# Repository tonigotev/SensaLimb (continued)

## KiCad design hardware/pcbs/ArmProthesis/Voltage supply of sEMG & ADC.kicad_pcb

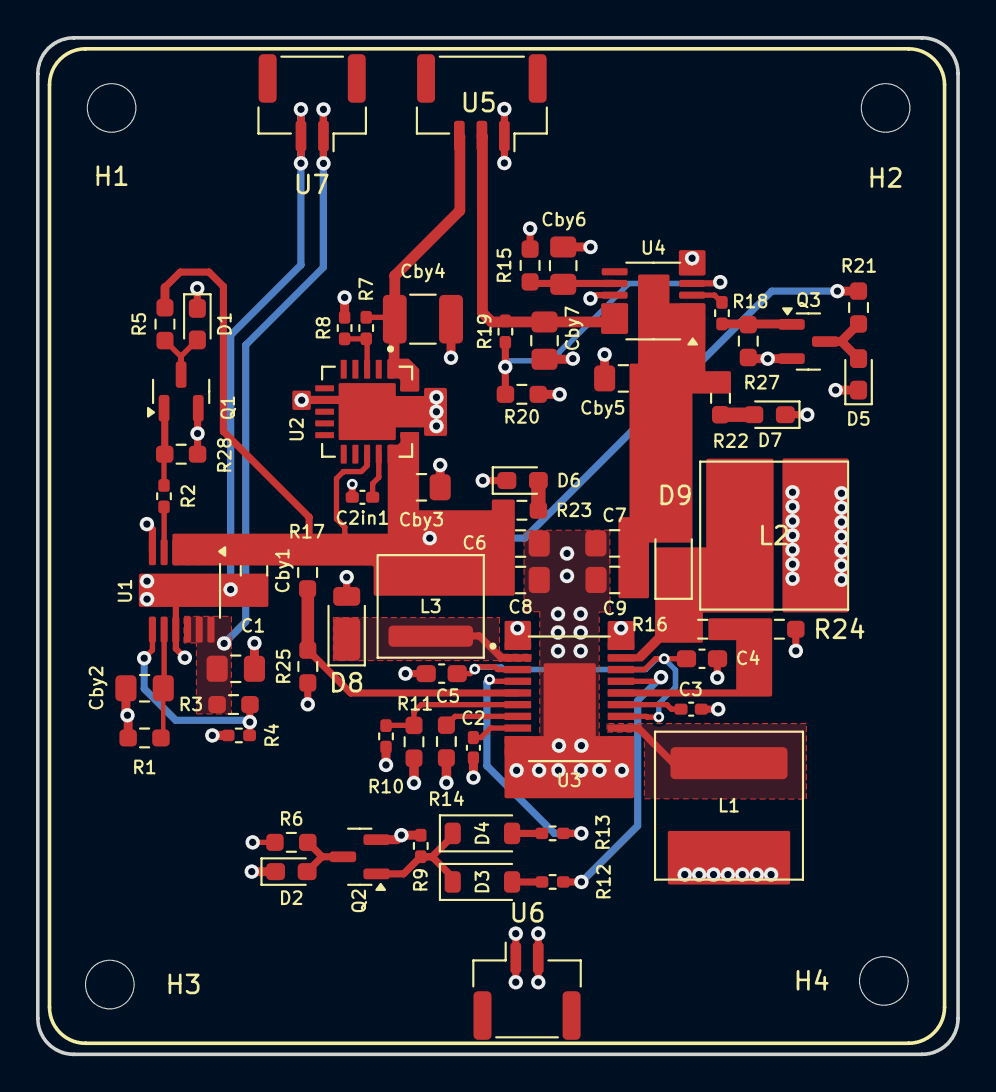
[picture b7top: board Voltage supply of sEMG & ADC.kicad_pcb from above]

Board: 4 copper layers, 51.1 x 56.5 mm, 70 parts (0 on the bottom side), 37 nets.

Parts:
C1, C6, C7, C8, C9: 10uF; C_0805_2012Metric_Pad1.18x1.45mm_HandSolder
C2, C3: 100nF; C_0402_1005Metric_Pad0.74x0.62mm_HandSolder
C2in1: 1uF; C_0402_1005Metric_Pad0.74x0.62mm_HandSolder
C4, C5: 1uF; C_0603_1608Metric_Pad1.08x0.95mm_HandSolder
Cby1, Cby3, Cby5, Cby7: 10uF; C_0805_2012Metric_Pad1.18x1.45mm_HandSolder
Cby2: 0.47uF; C_0805_2012Metric_Pad1.18x1.45mm_HandSolder
Cby4: 47uF; C_1210_3225Metric_Pad1.33x2.70mm_HandSolder
Cby6: 4.7uF; C_0805_2012Metric_Pad1.18x1.45mm_HandSolder
D1, D2, D5, D6, D7: LED; LED_0603_1608Metric_Pad1.05x0.95mm_HandSolder
D3, D4: D; D_SOD-123
D8: DFLS240L; D_PowerDI-123
D9: DFLS240; D_PowerDI-123
H1, H2, H3, H4: MountingHole; MountingHole_2.7mm_M2.5_DIN965
L1, L2: 6.8uH; L_Coilcraft_XAL7030-102
L3: 3.3uH; L_Coilcraft_XAL5030-XXX
Q1, Q2, Q3: BC817; SOT-23
R1: 49.9k; R_0603_1608Metric_Pad0.98x0.95mm_HandSolder
R2, R4, R8, R9, R12, R13, R18, R19: 10k; R_0402_1005Metric_Pad0.72x0.64mm_HandSolder
R3: 145k; R_0603_1608Metric_Pad0.98x0.95mm_HandSolder
R5, R6, R21: 5k; R_0603_1608Metric_Pad0.98x0.95mm_HandSolder
R7: 29.4k; R_0402_1005Metric_Pad0.72x0.64mm_HandSolder
R10: 23.7k; R_0402_1005Metric_Pad0.72x0.64mm_HandSolder
R11: 3.48k; R_0603_1608Metric_Pad0.98x0.95mm_HandSolder
R14: 85k; R_0603_1608Metric_Pad0.98x0.95mm_HandSolder
R15: 54.9k; R_0603_1608Metric_Pad0.98x0.95mm_HandSolder
R16, R17: 68k; R_0603_1608Metric_Pad0.98x0.95mm_HandSolder
R20: 147k; R_0603_1608Metric_Pad0.98x0.95mm_HandSolder
R22, R23: 1k; R_0603_1608Metric_Pad0.98x0.95mm_HandSolder
R24, R25, R27, R28: 10k; R_0603_1608Metric_Pad0.98x0.95mm_HandSolder
U1: LT3045xMSE; MSOP-12-1EP_3x4.039mm_P0.65mm_EP1.651x2.845mm
U2: TPS7A4701RGWR; QFN65P500X500X100-21N
U3: LT8471EFE_TRPBF; SOP65P640X120-21N
U4: LT3094xMSE; MSOP-12-1EP_3x4.039mm_P0.65mm_EP1.651x2.845mm
U5: JST_GH_SM03B-GHS-TB_1x03-1MP_P1.25mm_Horizontal
U6, U7: JST_GH_SM02B-GHS-TB_1x02-1MP_P1.25mm_Horizontal

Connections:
+6V: C6.1, C8.1, Cby1.1, Cby3.1, L3.2, R5.2, R17.1, R21.2, R23.1, U1.1 (IN), U1.2 (IN), U1.3 (IN), U1.4 (EN/UV), U2.13 (EN), U2.15 (IN_15), U2.16 (IN_16)
-6V: C7.2, C9.2, Cby5.1, D9.2 (A), R22.1, U4.1 (IN), U4.2 (IN), U4.3 (EN/UV), U4.13 (IN)
/+5.5V: Cby4.1, R7.1, U2.1 (OUT_1), U2.20 (OUT_20), U5.3
/+5V: C1.1, R3.2, U1.10 (OUTS), U1.11 (OUT), U1.12 (OUT), U7.1
/+11.1V: L1.1, R6.2, R10.2, U3.1 (C1), U3.20 (C2), U6.1
/-5.5V: Cby7.1, R19.1, U4.10 (OUTS), U4.11 (OUT), U4.12 (OUT), U5.2
GND: C1.2, C2.2, C2in1.2, C3.2, C4.1, C5.2, C6.2, C7.1, C8.2, C9.1, Cby1.2, Cby2.2, Cby3.2, Cby4.2, Cby5.2, Cby6.2, Cby7.2, D1.1 (K), D2.1 (K), D5.1 (K), D6.1 (K), D7.1 (K), D8.2 (A), L2.1, Q1.2 (E), Q2.2 (E), Q3.2 (E), R1.2, R4.1, R8.2, R9.2, R11.1, R14.2, R15.2, R20.2, R24.2, R25.2, R27.2, R28.2, U1.6 (ILIM), U1.9 (GND), U1.13 (GND), U2.7 (GND_7), U2.17 (NC_17), U2.18 (NC_18), U2.19 (NC_19), U2.21 (GND_21), U3.9 (SYNC), U3.10 (GND), U3.11 (GND), U3.12 (GND), U3.21 (GND), U4.6 (ILIM), U4.9 (GND), U5.1, U6.2, U7.2
unnamed: D1.2 (A), Q1.3 (C), R5.1
unnamed: D2.2 (A), Q2.3 (C), R6.1
unnamed: D3.2 (A), R12.2
unnamed: D3.1 (K), D4.1 (K), Q2.1 (B), R9.1
unnamed: D4.2 (A), R13.2
unnamed: D5.2 (A), Q3.3 (C), R21.1
unnamed: D6.2 (A), R23.2
unnamed: D7.2 (A), R22.2
unnamed: D8.1 (K), L3.1, U3.2 (E1)
unnamed: D9.1 (K), L2.2, R16.1, U3.19 (E2)
unnamed: Q1.1 (B), R2.2, R28.1
unnamed: Q3.1 (B), R18.2, R27.1
unnamed: R2.1, U1.5 (PG)
unnamed: R3.1, R4.2, U1.7 (PGFB)
unnamed: Cby2.1, R1.1, U1.8 (SET)
unnamed: C2in1.1, U2.14 (NR)
unnamed: R7.2, R8.1, U2.3 (SENSE/FB)
unnamed: L1.2, U3.13 (C3)
unnamed: R17.2, R25.1, U3.5 (FB1)
unnamed: R16.2, R24.1, U3.16 (FB2)
unnamed: R10.1, R11.2, U3.6 (OV/UV)
unnamed: R13.1, U3.4 (PG1)
unnamed: R12.1, U3.17 (PG2)
unnamed: R14.1, U3.7 (RT)
unnamed: C4.2, C5.1, U3.3 (VIN1), U3.14 (SHOUT), U3.18 (VIN2)
unnamed: C2.1, U3.8 (SS1)
unnamed: C3.1, U3.15 (SS2)
unnamed: R18.1, U4.4 (PG)
unnamed: R19.2, R20.1, U4.5 (PGFB)
unnamed: Cby6.1, R15.1, U4.8 (SET)

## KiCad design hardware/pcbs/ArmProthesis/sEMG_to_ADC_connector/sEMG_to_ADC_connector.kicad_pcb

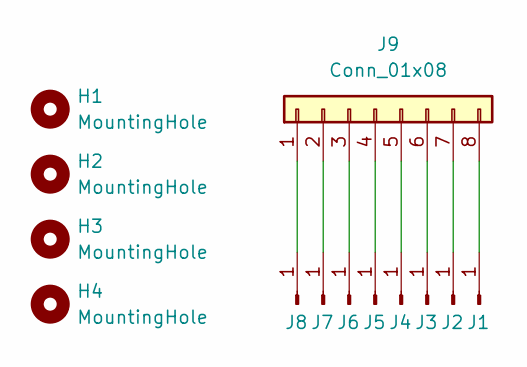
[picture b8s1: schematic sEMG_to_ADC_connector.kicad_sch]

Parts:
H1, H2, H3, H4: MountingHole; MountingHole_2.7mm_M2.5
J1, J2, J3, J4, J5, J6, J7, J8: Conn_01x01_Pin; DIN_Male_1PIN_1.5mm
J9: Conn_01x08; JST_GH_SM08B-GHS-TB_1x08-1MP_P1.25mm_Horizontal

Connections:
unnamed: J1.1, J9.8
unnamed: J2.1, J9.7
unnamed: J3.1, J9.6
unnamed: J4.1, J9.5
unnamed: J5.1, J9.4
unnamed: J6.1, J9.3
unnamed: J7.1, J9.2
unnamed: J8.1, J9.1

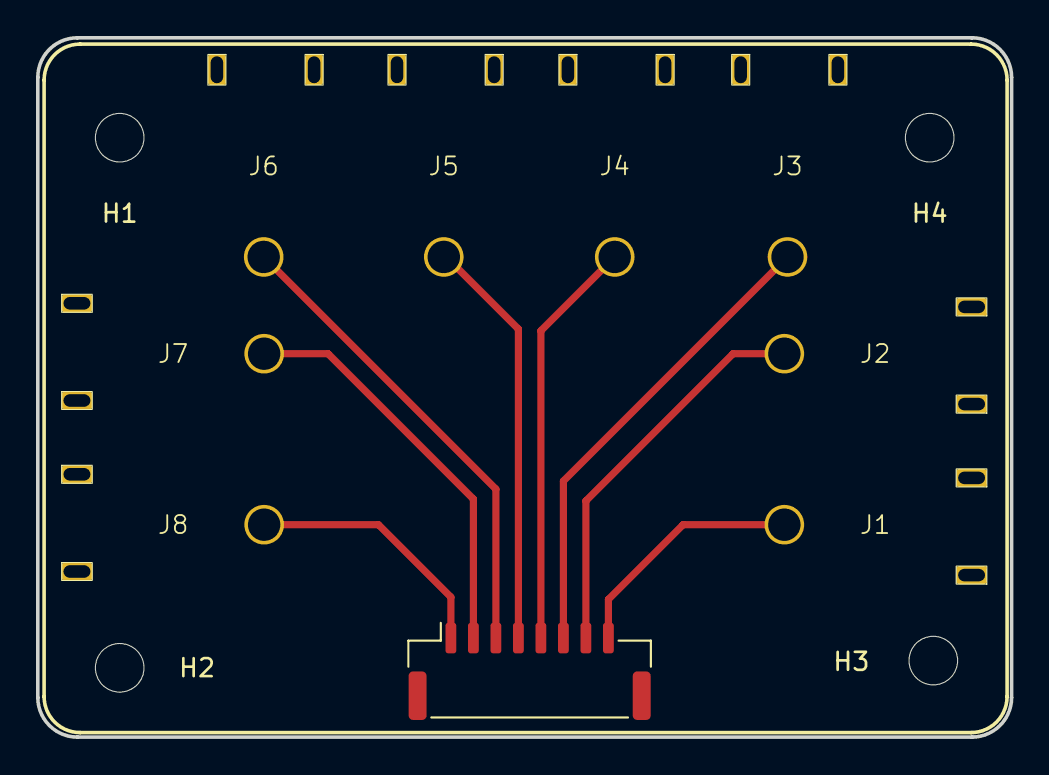
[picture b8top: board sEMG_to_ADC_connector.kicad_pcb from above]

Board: 2 copper layers, 54.1 x 38.9 mm, 13 parts (0 on the bottom side), 8 nets.

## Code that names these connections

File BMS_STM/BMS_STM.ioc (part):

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Mcu.Name=STM32C011F(4-6)Px
Mcu.Package=TSSOP20
Mcu.UserName=STM32C011F6Px
PA13.Mode=Serial_Wire
PA13.Signal=DEBUG_SWDIO
PA14-BOOT0.Mode=Serial_Wire
PA14-BOOT0.Signal=DEBUG_SWCLK
PA2.Mode=Half_duplex(single_wire_mode)
PA2.Signal=USART2_TX
PA8.Signal=GPXTI8
PB6.Mode=I2C
PB6.Signal=I2C1_SCL
PB7.Mode=I2C
PB7.Signal=I2C1_SDA
PC14-OSCX_IN\ (PC14).Mode=LSE-External-Oscillator
PC14-OSCX_IN\ (PC14).Signal=RCC_OSCX_IN
PC15-OSCX_OUT\ (PC15).Mode=LSE-External-Oscillator
PC15-OSCX_OUT\ (PC15).Signal=RCC_OSCX_OUT
RCC.HSE_VALUE=8000000
RCC.SYSCLKFreq_VALUE=12000000
board=custom

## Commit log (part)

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2025-09-12 Voltage supply of sEMG & ADC
2025-09-14 EMG sensor v0.2
2025-09-18 sEMG sensors v0.3
2025-09-18 Fixes
    sEMG - minor
    Voltage supply... - major but not fixed
2025-09-18 Additional to last push
2025-09-18 Voltage supply sEMG & ADC v0.2
    Major fixes. Mounting holes missing
2025-09-21 BMS v0.2v + polishment of Vsupply board
2025-09-21 Connector update of the sEMG sensor
    Changed it to be JST_GH_SM04B instead of JST_GH_BM04B for easier use
2025-09-22 ADC + sEMG changes
    sEMG - connector updates
    ADC - major changes - connectors, layout changes
2025-09-23 BMS v0.3 + main folder reconstruction
2025-09-23 sEMG critical issue
    Corrected inaccurate DIN 1.5mm jack footprint
2025-09-23 Cosmetics xd
2025-10-27 Vs of sEMG and ADC v0.4
2025-11-03 Corrected BMS connection
2025-11-04 BMS v0.5 still not resized
2026-01-13 Mendeley data set + plotter
    Analyzing data sets and beginning to develop the ML algorithm for the arm
2026-01-13 Normalizer + plotter(upgraded
    Normalizer for the data.
    Plotter has new functionalities such as - plot all subjects data and distribute them to new folders, calculate db/frequency for a new plot etc.
2026-01-19 Fix Vsupply
    added important Schottky diodes on the BUCK
2026-01-19 New
    Mendeley dataset is not good enough for angle regression or for 3 class classifier.
    Moved on to Toro Ossaba's dataset specifically designed for training ML algorithms - smooth kinetic transitions.
    Trainers for several ML models have been implemented but the most successful one is conv1d_angle_toro_ossaba. This exact model doesn't extract features but lets the model extrarct them by 3 convoluti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
2026-01-20 Fixed EMG sensors active band pass filter
2026-01-20 new LDO with a proper rail splitter
2026-01-21 Fixed LCSC numbers of the new filter parts
2026-01-24 Fixed compatibility of connectors + new BMS chip
2026-01-24 bms V0.7 with BQ76905
2026-01-28 BMS board fixes
2026-02-01 Ordered versions
2026-02-05 Configure BQ76905 protections and alert handling
    Add concrete DM config values for alarms, enabled protections, and FET trip mapping, plus ADSCAN-based CUV/COV delay calculation and SCD delay placeholder.
    Implement full alert decision flow: status-first handling, XDSG timeout adjustment, fault bookkeeping, low-battery percent polling/warning, and Nucleo action hooks/stubs.
2026-02-06 Finalize BMS config, alert actions, and UART framing
    Add concrete DM configuration (alarm mask, protection enables, FET trip mapping, CUV/COV thresholds/delays/hysteresis, SCD code) and reliable CFGUPDATE init with FET enable and alarm clear.
    Implement full alert/status handling with last-fault reporting/retry, low-batt percent polling, and UART framing (seq + CRC8).
2026-02-06 Moved the files to the correct folder
    Apparently I have been working outside of the BMS-STM folder without realizing it...
2026-02-06 UART RX implementation with empty action functions
2026-02-06 Add AD7606 driver and relocate UART RX code
    Introduce AD7606 parallel read scaffolding with DWT timing helpers.
    Move UART RX implementation into NUCLEO/UART and remove old paths.
2026-02-09 Main function reallocated + down sampling logic fixed
2026-02-09 UART DMA + IDLE interrupt integration template.
2026-02-10 Refactor control loop and add ML assets
    Split sampling/RMS/ANN logic into dedicated modules and simplify main loop.
    Implemented the correct flow for reading the samples, processing them into input vectors for the ANN.
    The exact function for parsing those inputs into the ANN are still not implemented.
    Add ML models/assets folder used for prosthesis inference workflows.
2026-02-16 Retrained several models and changed input layer
    Newer models now accept 3x200 samples instead of 205.
2026-02-16 Create .gitignore
    Ignoring the datasets due to their extreme size.
2026-02-16 wire UART DMA + fake ADC data path + STM32 project architecture
    Move the nucleo app sources into the STM32 project layout, hook the control
    loop into main, and add UART DMA/IDLE RX processing. Add a fake ADC data
    table path to test RMS → ANN parsing without hardware.
2026-02-16 Revert "First version meant to be deployed to the NUCLEO"
2026-02-23 Sync latest Nucleo firmware and timing architecture.
    Integrate ISR-based 1 kHz sampling with 50 ms rolling-window inference, stabilize UART/diagnostic logging, and align project/docs with the current STM32U575 workflow and fake-data validation path.
2026-02-26 Remove unrelated KiCad projects after import
    The original KiCad repo contained multiple projects; keep only SensaLimb-related boards under hardware/pcbs.
2026-02-26 Clean old/unused Gerbers and backup files from KiCad project
2026-02-26 Synced the files with the latest versions
    The files that were merged were one version behind. Also the names of the projects were renamed for clarity.
2026-02-27 Cleared zip backup folders + old boms
2026-02-27 Align angle-history preprocessing with ML training pipeline
    Switch context-angle generation to a 1 kHz ring buffer, apply a 0.1 s lag at sample level, and downsample to 200 Hz per inference window. Also align ANN angle normalization/de-normalization with trai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
2026-05-12 BMS_STM STM32C011F6Px project setup
    Set up a bare STM32CubeIDE project for the BMS MCU (STM32C011F6Px) targeting the BQ76905 2-cell BMS IC. Configured I2C1 (PB6/PB7) for BQ76905 communication, USART2 (PA2) for TX logging to the Nucleo,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
2026-05-12 Removed old and unused dataset from repo
2026-05-12 Clarification for readme
2026-05-16 Enable VddIO2 for port G - fixes DB7/DB8
2026-05-17 AD7606 parallel read working - all 16 bits
2026-05-18 fix(ad7606): correct ADC control pin assignments — restore conversions
    The AD7606 was not converting due to three independent pin-assignment
    faults, all rooted in pins being assigned without checking existing
    board/silicon functions.
    CONVST (was PC13 -> now PE3)
    PC13 is a backup-domain pin with weak drive; it produced a 10-12us
    RC-curve rising edge instead of a sharp digital edge, so the AD7606
2026-05-27 Added PDF schematics of the pcbs
2026-05-27 Remove old BMS-STM folder
